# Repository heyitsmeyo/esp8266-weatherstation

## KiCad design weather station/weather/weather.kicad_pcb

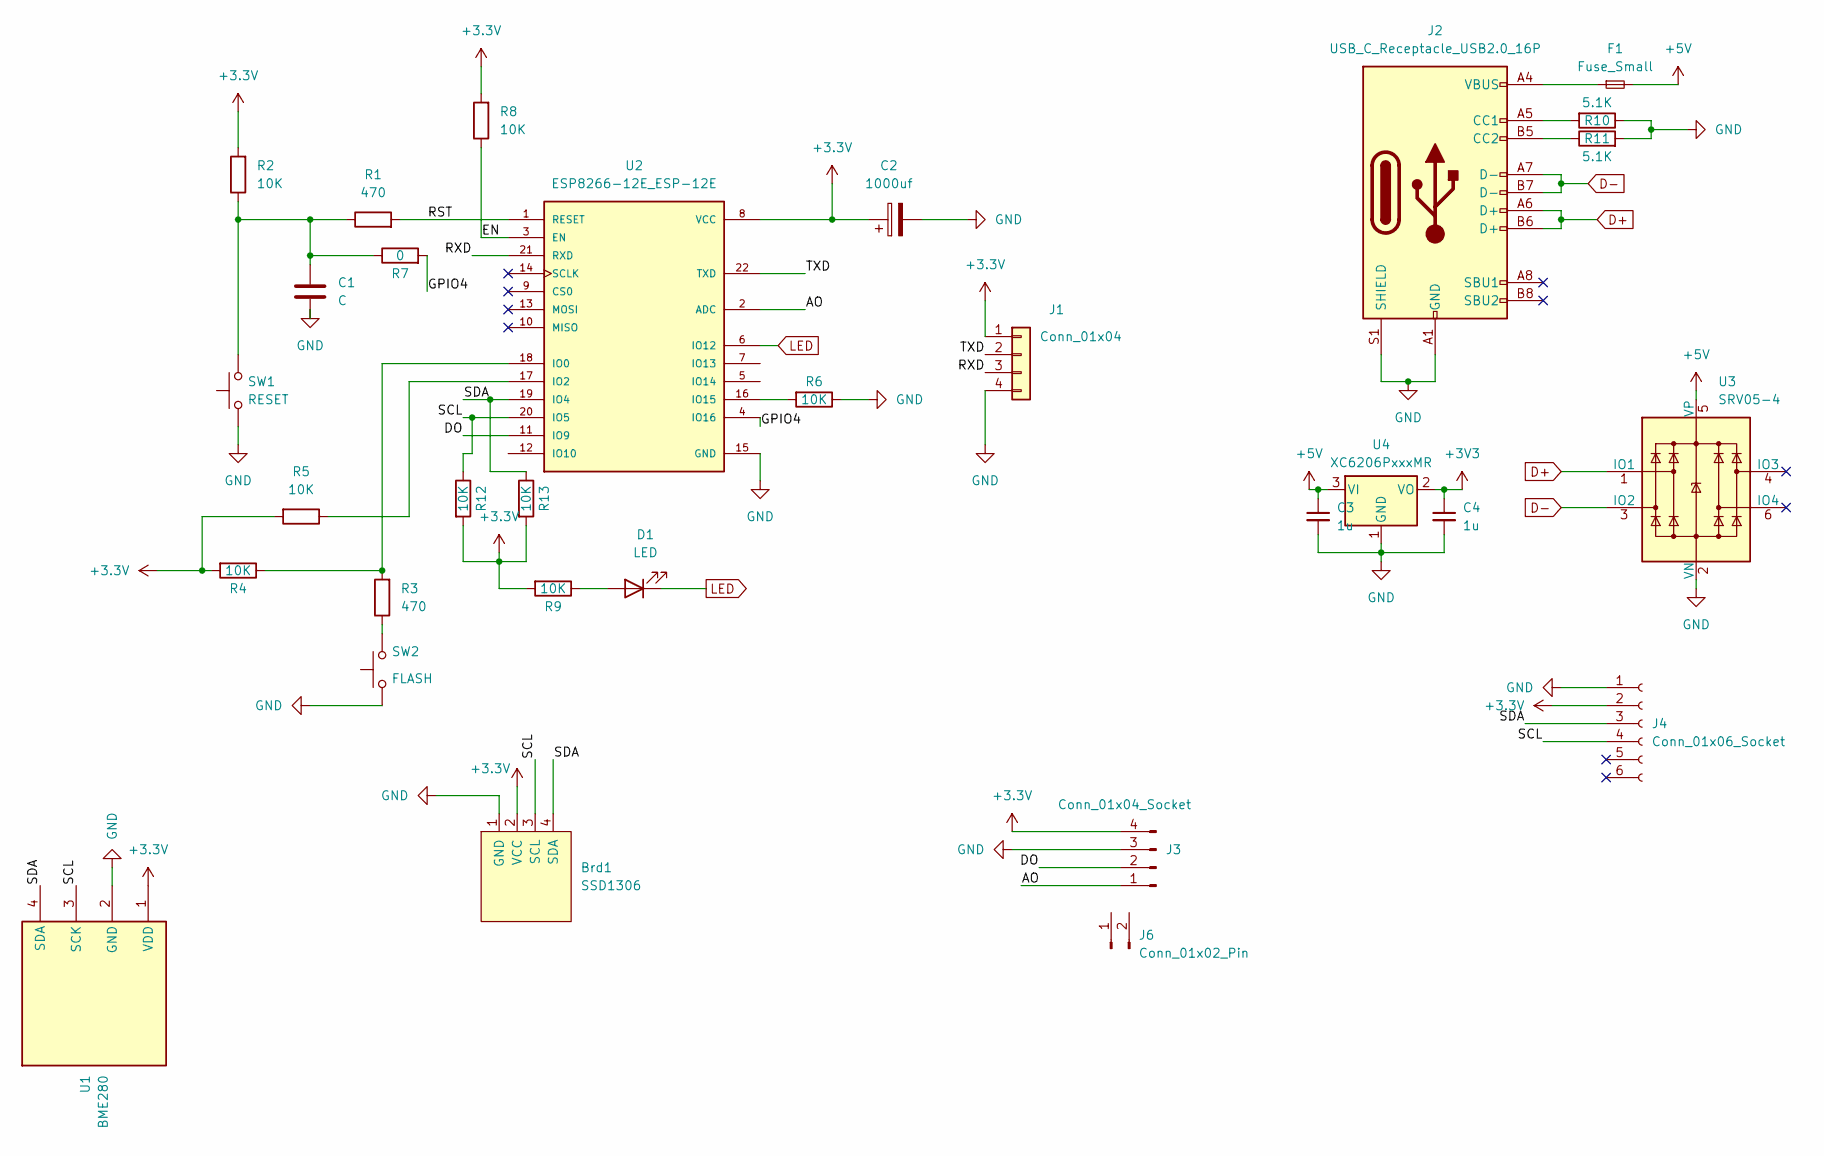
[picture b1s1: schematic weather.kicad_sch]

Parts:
Brd1: SSD1306; 128x64OLED
C1: C; C_0603_1608Metric
C2: 1000uf; C_0402_1005Metric
C3, C4: 1u; C_0402_1005Metric
D1: LED; LED_0201_0603Metric
F1: Fuse_Small; Fuse_1206_3216Metric
J1: Conn_01x04; JST_SH_SM04B-SRSS-TB_1x04-1MP_P1.00mm_Horizontal
J2: USB_C_Receptacle_USB2.0_16P; USB_C_Receptacle_HRO_TYPE-C-31-M-12
J3: Conn_01x04_Socket; PinHeader_1x04_P2.54mm_Vertical
J4: Conn_01x06_Socket; PinSocket_1x06_P2.54mm_Horizontal
J6: Conn_01x02_Pin; PinHeader_1x02_P2.54mm_Vertical
R1, R3: 470; R_0603_1608Metric
R2, R4, R5, R6, R8, R9, R12, R13: 10K; R_0603_1608Metric
R7: 0; R_0603_1608Metric
R10, R11: 5.1K; R_0402_1005Metric
SW1: RESET; SW_PUSH_6mm
SW2: FLASH; SW_PUSH_6mm
U1: BME280; PinSocket_1x04_P2.54mm_Vertical
U2: ESP8266-12E_ESP-12E; XCVR_ESP8266-12E_ESP-12E
U3: SRV05-4; SOT-23-6
U4: XC6206PxxxMR; SOT-23-3

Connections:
+3.3V: Brd1.2 (VCC), C2.1, J1.1, J3.4, J4.2, R2.2, R4.2, R5.2, R8.2, R9.2, R12.2, R13.2, U1.1 (VDD), U2.8 (VCC); also elsewhere on the board
+3V3: C4.1, U4.2 (VO); also elsewhere on the board
+5V: C3.1, F1.2, U3.5 (VP), U4.3 (VI); also elsewhere on the board
/AO: J3.1, U2.2 (ADC)
/DO: J3.2, U2.11 (IO9)
/EN: R8.1, U2.3 (EN)
/GPIO4: R7.2, U2.4 (IO16)
/RST: R1.2, U2.1 (RESET)
/RXD: J1.3, U2.21 (RXD)
/SCL: Brd1.3 (SCL), J4.4, R12.1, U1.3 (SCK), U2.20 (IO5); also elsewhere on the board
/SDA: Brd1.4 (SDA), J4.3, R13.1, U1.4 (SDA), U2.19 (IO4); also elsewhere on the board
/TXD: J1.2, U2.22 (TXD)
D+: J2.A6 (D+), J2.B6 (D+), U3.1 (IO1)
D-: J2.A7 (D-), J2.B7 (D-), U3.3 (IO2)
GND: Brd1.1 (GND), C1.2, C2.2, C3.2, C4.2, J1.4, J2.A1 (GND), J2.A12 (GND), J2.B1 (GND), J2.B12 (GND), J2.S1 (SHIELD), J3.3, J4.1, R6.1, R10.1, R11.2, SW1.1, SW2.1, U1.2 (GND), U2.15 (GND), U3.2 (VN), U4.1 (GND); also elsewhere on the board
LED: D1.1 (K), U2.6 (IO12)
unnamed: C1.1, R1.1, R2.1, R7.1, SW1.2
unnamed: D1.2 (A), R9.1
unnamed: F1.1, J2.A4 (VBUS), J2.A9 (VBUS), J2.B4 (VBUS), J2.B9 (VBUS)
unnamed: J2.A5 (CC1), R10.2
unnamed: J2.B5 (CC2), R11.1
unnamed: R3.1, SW2.2
unnamed: R3.2, R4.1, U2.18 (IO0)
unnamed: R5.1, U2.17 (IO2)
unnamed: R6.2, U2.16 (IO15)

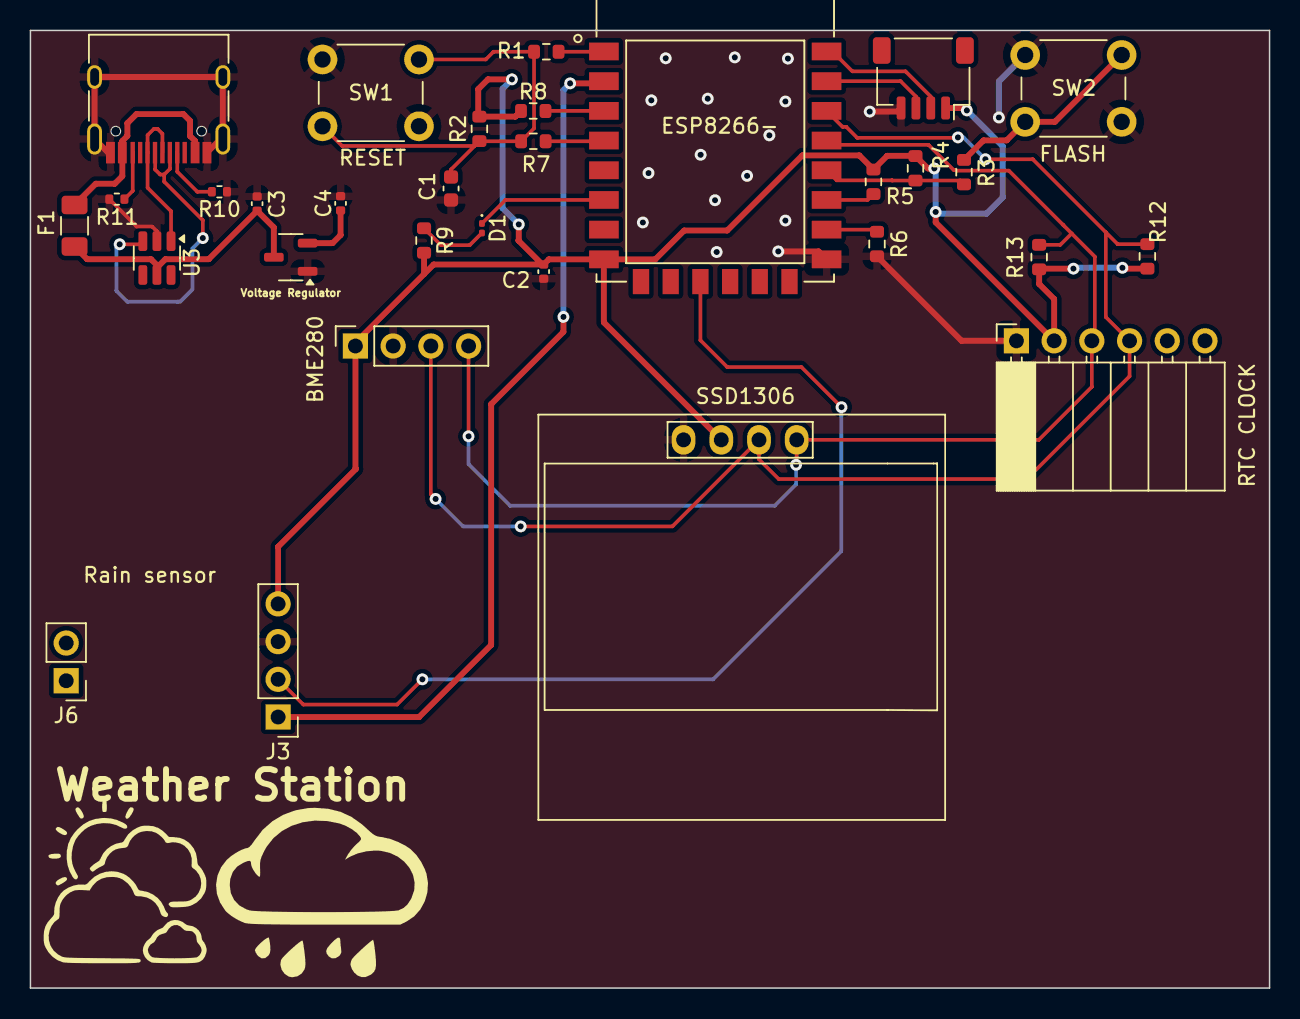
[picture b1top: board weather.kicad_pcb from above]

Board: 2 copper layers, 83.5 x 64.5 mm, 31 parts (0 on the bottom side), 25 nets.

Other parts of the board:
BME280: BME280; PinSocket_1x04_P2.54mm_Vertical
RTC CLOCK: Conn_01x06_Socket; PinSocket_1x06_P2.54mm_Horizontal
Voltage Regulator: XC6206PxxxMR; SOT-23-3

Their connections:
+3.3V: BME280.1 (VDD), RTC CLOCK.2; also elsewhere on the board
+3V3: Voltage Regulator.2 (VO); also elsewhere on the board
+5V: Voltage Regulator.3 (VI); also elsewhere on the board
/SCL: BME280.3 (SCK), RTC CLOCK.4; also elsewhere on the board
/SDA: BME280.4 (SDA), RTC CLOCK.3; also elsewhere on the board
GND: BME280.2 (GND), RTC CLOCK.1, Voltage Regulator.1 (GND); also elsewhere on the board
